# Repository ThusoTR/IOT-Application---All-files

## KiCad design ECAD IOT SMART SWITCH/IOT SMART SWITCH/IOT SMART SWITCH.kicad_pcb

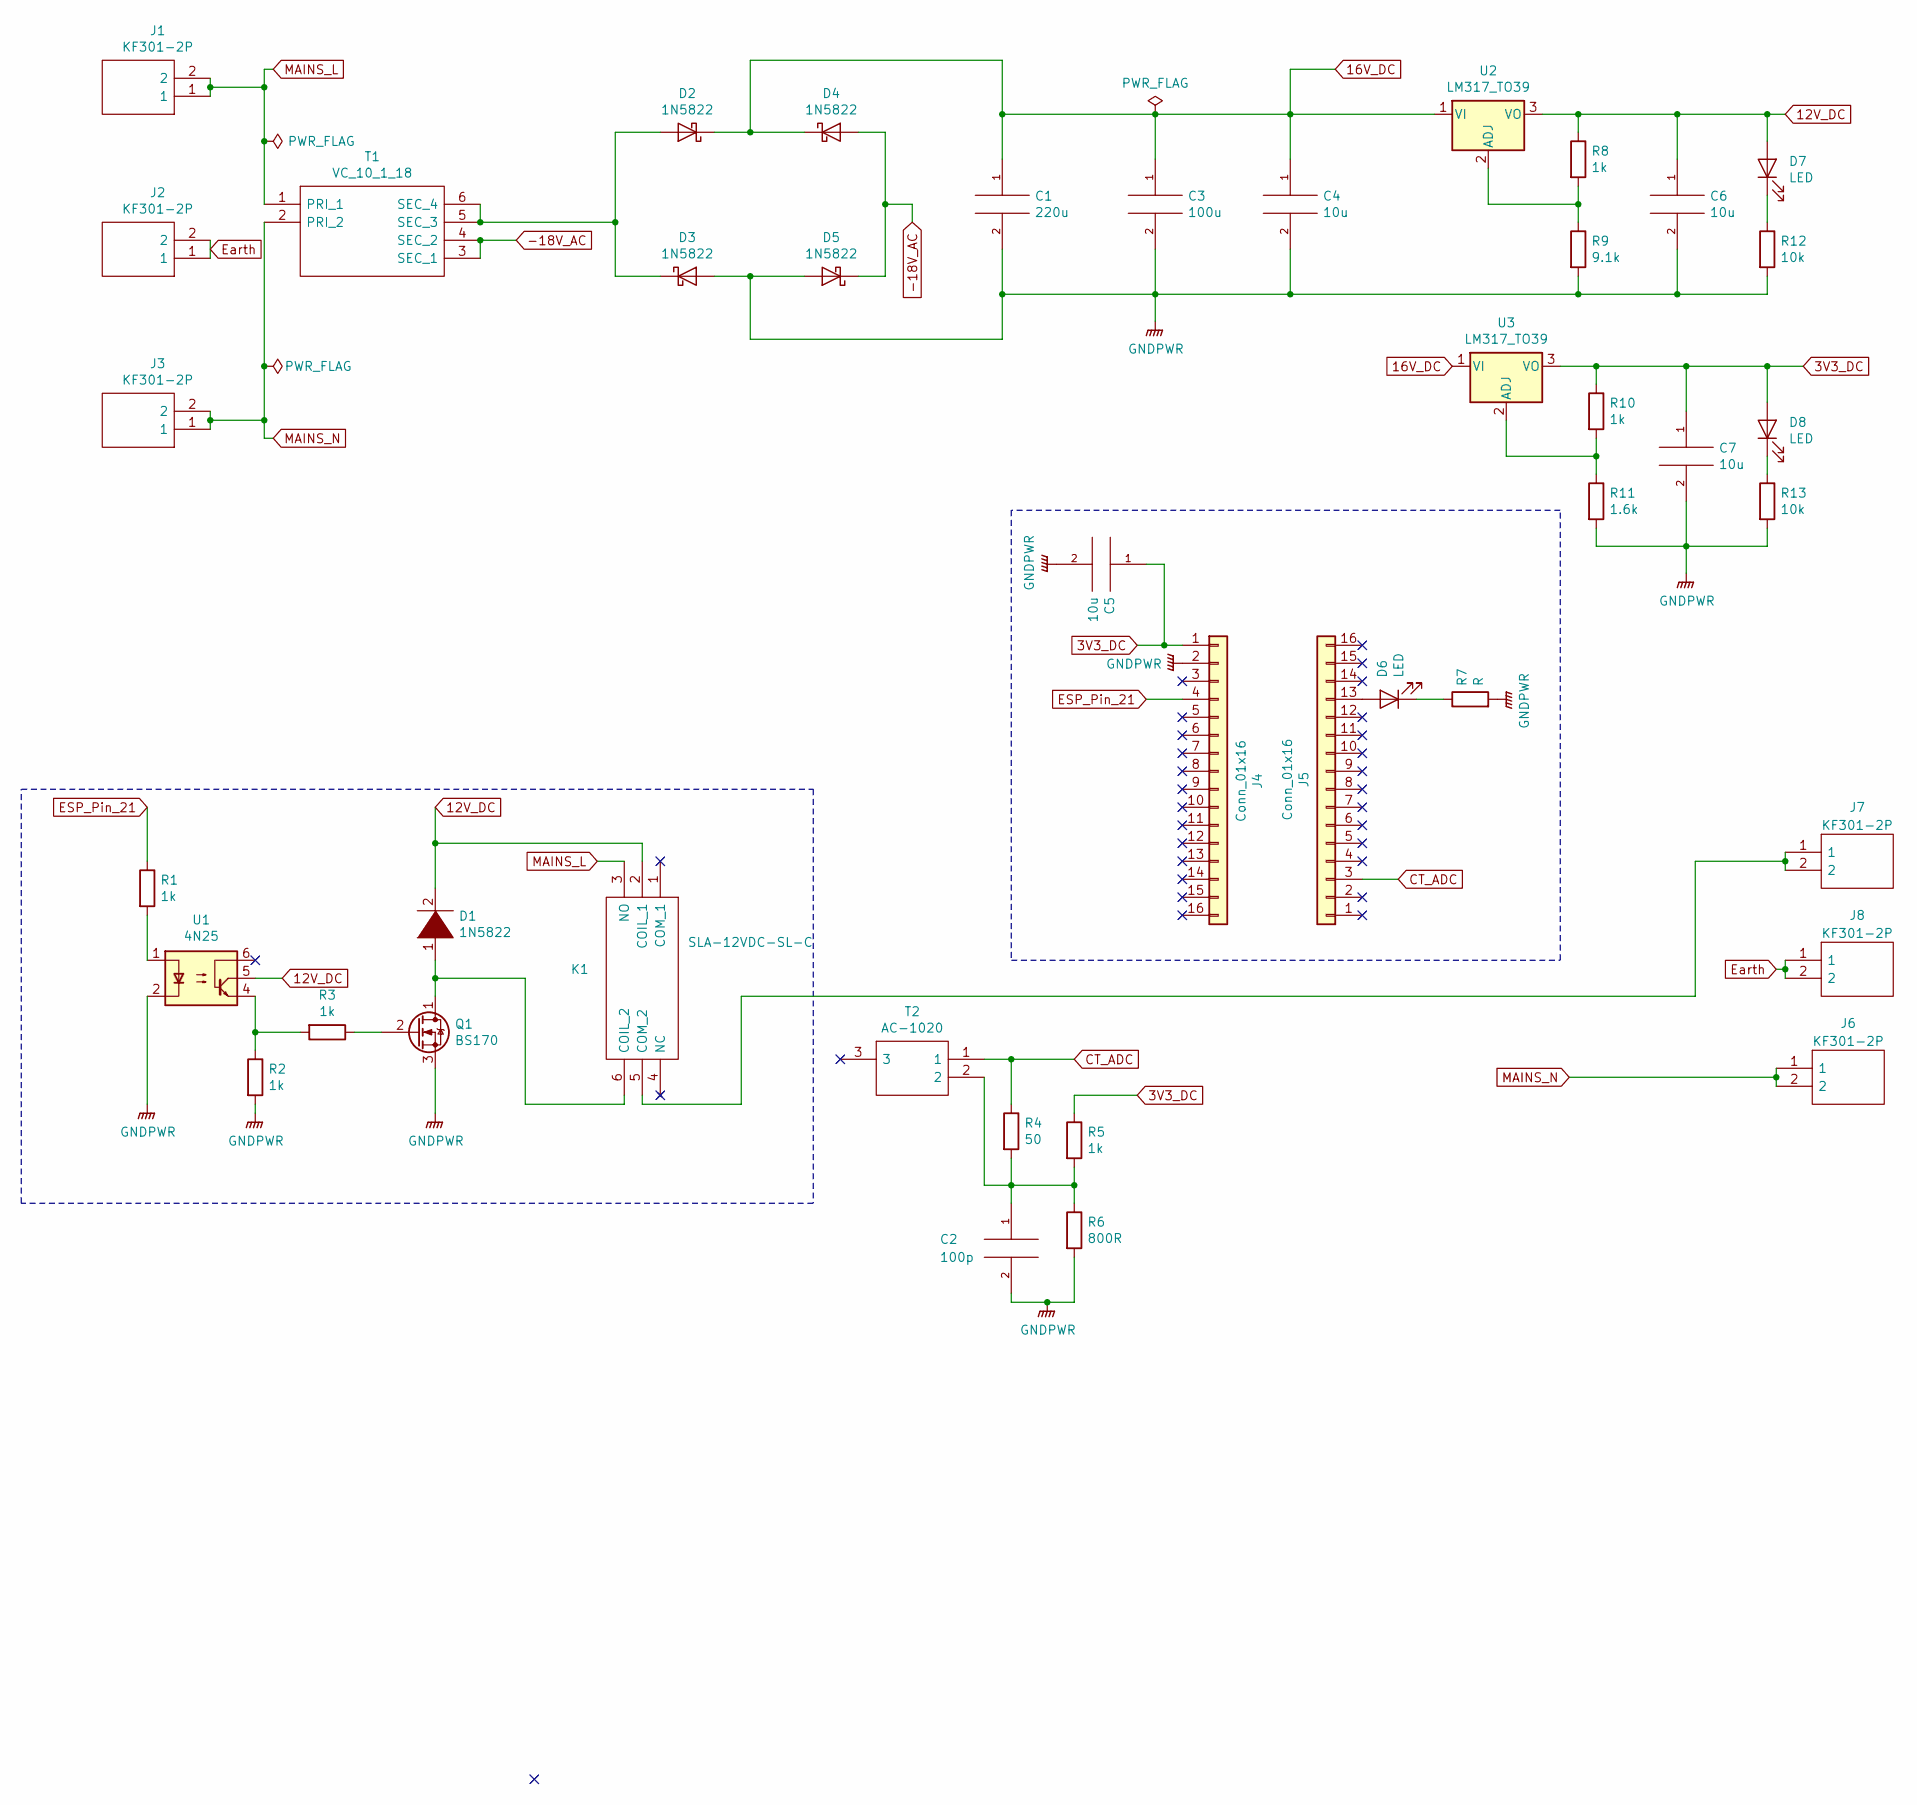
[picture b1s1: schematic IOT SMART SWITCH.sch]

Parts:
C1: 220u; CP_Radial_D6.3mm_P2.50mm
C2: 100p; CP_Radial_D5.0mm_P2.00mm
C3: 100u; CP_Radial_D5.0mm_P2.00mm
C4, C5, C6, C7: 10u; CP_Radial_D5.0mm_P2.00mm
D1, D2, D3, D4, D5: 1N5822; D_DO-201AD_P15.24mm_Horizontal
D6, D7, D8: LED; LED_D3.0mm
J1, J2, J3, J6, J7, J8: KF301-2P; KF3012P; Manufacturer_Part_Number KF301-2P
J4, J5: Conn_01x16; PinSocket_1x16_P2.54mm_Vertical
K1: SLA-12VDC-SL-C; SLA12VDCSLC; Manufacturer_Part_Number SLA-12VDC-SL-C
Q1: BS170; TO-92_Inline
R1, R2, R3, R5, R8, R10: 1k; R_1206_3216Metric
R4: 50; R_1206_3216Metric
R6: 800R; R_1206_3216Metric
R7: R; R_1206_3216Metric
R9: 9.1k; R_1206_3216Metric
R11: 1.6k; R_1206_3216Metric
R12, R13: 10k; R_1206_3216Metric
T1: VC_10_1_18; VC10118; Manufacturer_Part_Number VC 10/1/18
T2: AC-1020; AC1015; Manufacturer_Part_Number AC-1020
U1: 4N25; DIP-6_W7.62mm
U2, U3: LM317_TO39; TO255P460X1020X2008-3P

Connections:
3V3_DC: C5.1, C7.1, D8.2 (A), J4.1, R5.1, R10.1, U3.3 (VO)
12V_DC: C6.1, D1.2 (A), D7.2 (A), K1.2 (COIL_1), R8.1, U1.5, U2.3 (VO)
16V_DC: C1.1, C3.1, C4.1, D2.1 (K), D4.1 (K), U2.1 (VI), U3.1 (VI)
-18V_AC: D4.2 (A), D5.1 (K), T1.3 (SEC_1), T1.4 (SEC_2)
CT_ADC: J5.3, R4.1, T2.1
ESP_Pin_21: J4.4, R1.1
Earth: J2.1, J2.2, J8.1, J8.2
GNDPWR: C1.2, C2.2, C3.2, C4.2, C5.2, C6.2, C7.2, D3.2 (A), D5.2 (A), J4.2, Q1.3 (S), R2.2, R6.2, R7.2, R9.2, R11.2, R12.2, R13.2, U1.2
MAINS_L: J1.1, J1.2, K1.3 (NO), T1.1 (PRI_1)
MAINS_N: J3.1, J3.2, J6.1, J6.2, T1.2 (PRI_2)
unnamed: C2.1, R4.2, R5.2, R6.1, T2.2
unnamed: D1.1 (K), K1.6 (COIL_2), Q1.1 (D)
unnamed: D2.2 (A), D3.1 (K), T1.5 (SEC_3), T1.6 (SEC_4)
unnamed: D6.1 (K), R7.1
unnamed: D6.2 (A), J5.13
unnamed: D7.1 (K), R12.1
unnamed: D8.1 (K), R13.1
unnamed: J7.1, J7.2, K1.5 (COM_2)
unnamed: Q1.2 (G), R3.1
unnamed: R1.2, U1.1
unnamed: R2.1, R3.2, U1.4
unnamed: R8.2, R9.1, U2.2 (ADJ)
unnamed: R10.2, R11.1, U3.2 (ADJ)

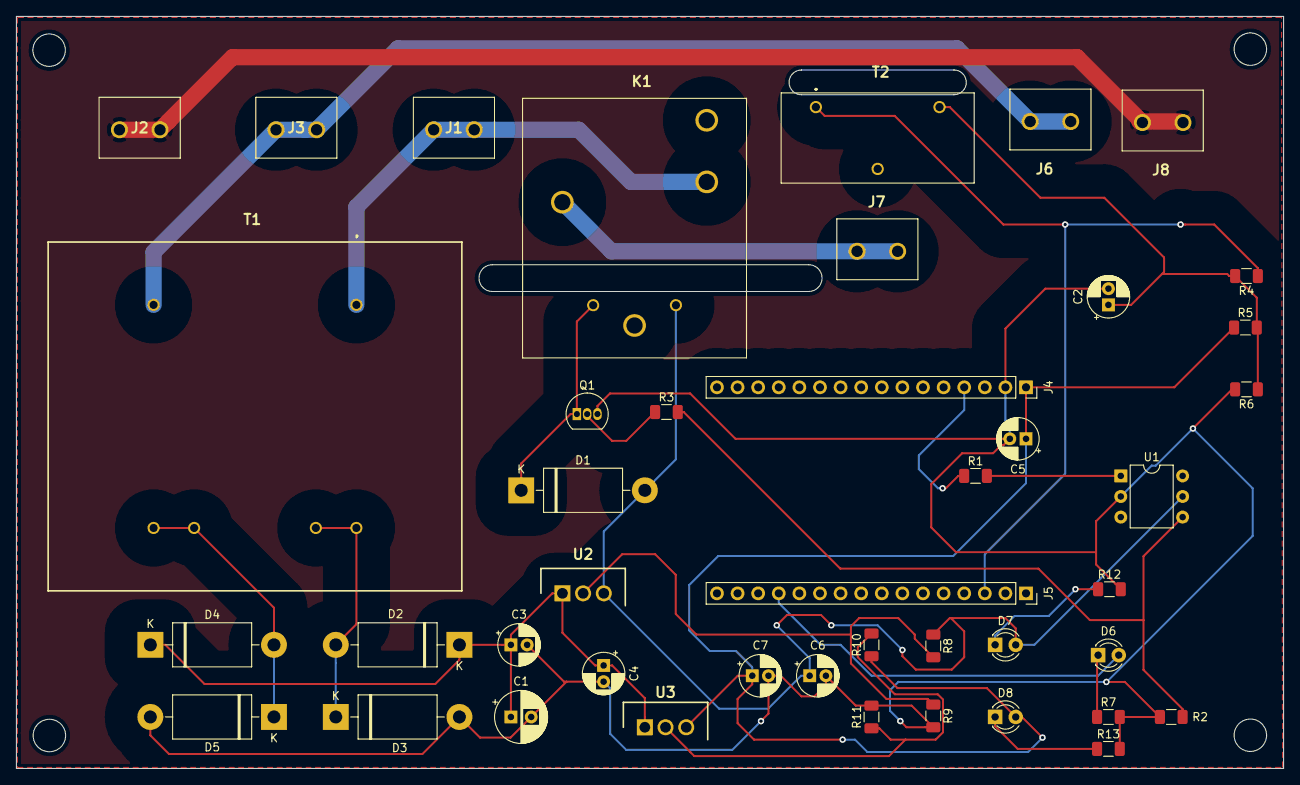
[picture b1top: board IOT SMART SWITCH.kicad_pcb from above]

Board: 2 copper layers, 156.2 x 92.7 mm, 43 parts (0 on the bottom side), 23 nets.

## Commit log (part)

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2021-05-25 The Start up
2021-05-26 Project Started
2021-05-28 work in progress
2021-06-01 Finish up schematic
2021-06-08 Associations are tough
2021-06-09 Not within budget
2021-06-10 Associate last pieces
2021-06-11 PCB New Start
2021-06-13 eeschema updated
2021-06-14 Is fridge running
2021-06-14 then go run after it
2021-06-14 Ready for quotes
2021-06-16 Kicad project done for now
2021-06-17 RE-Think Things
2021-06-18 Its costly to develop
